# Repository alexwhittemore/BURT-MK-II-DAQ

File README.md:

BURT Mk-II DAQ
==============

Boston University Rocket Team's Mk-II Data Acquisition and Control System.

Background
----------
The Boston University Rocket Team is currently focused on advancing hybrid rocket motor design and research. The Mk-II is a static (never leaves the ground) test bed for experimentation with various design parameters like chamber and oxidizer injector geometries.

### Sensors
The DAQ side consists of multiple sensors: pressure transducers, load cells, and thermocouples.

There are two pressure transducers, each rated at 500PSI full scale. The Oxidizer Line Transducer measures the pressure on the nitrous oxide feed line right before the injector. This should match the vapor pressure of N2O, roughly 750PSI dependent on temperature. The Combustion Chamber Transducer measures the pressure INSIDE the combustion chamber, directly after the injector. For Mk-II, the design chamber pressure is 500PSI

There are also two load cells. The Thrust Load Cell is an S-Beam, 500lbs full scale load cell. Design thrust is 75lbs. The Oxidizer Tank Cell is a canteliver 50lbs cell. This measures the weight of the Nitrous Oxide tank used to feed the motor, where change in mass of the tank can be used to calculate mass flow rate of oxidizer.

There are three thermocouples. All are K-type. One NPT-threaded, sealed TC measures oxidizer temperature before the injector. One of two silicone surface adhesive TCs measures the oxidizer tank temperature. The other of these measures the combustion chamber casing temperature. A spike in this temperature indicates a fault with the fuel grain casting and a potentially unsafe conditon that could result in a burn-through of the schedule-80 steel casing.

### Boards
All of these are read by four wheatstone bridge digitizer boards (Bridge Digitizer.sch) and three K-type thermocouple digitizer boards (Thermocouple Digitizer.sch). The outputs of these boards are read via SPI by an mbed microcontroller residing on a main board. This main board also holds a zigbee radio which forwards a UART connection to a host computer for off-site (safe distance) live monitoring of the system, as well as a USB plug for a thumb drive to log the live, real-time acquired data. Additionally, a UART is broken out on a set of .1" spaced headers to connect to a sparkfun graphical LCD for on-site monitoring. Finally, two pins are broken out on a DB-9 connector to serve as software serial to a safe distance physical control interface. This could just as easily be run exclusively via zigbee radio.

### Control
The final job of the system is to control the burn itself. This is handled by two pneumatic valves, switched by 24-volt electric solenoids in turn controlled by the mbed via a quad-half H-bridge chip on the main board. These solenoids are either open or spring-shut, and thus only require two outputs of the quad half Bridge. A third output is used to control a nichrome wire-based pyrotechnic ignitor. The fourth half bridge is implemented but unused.

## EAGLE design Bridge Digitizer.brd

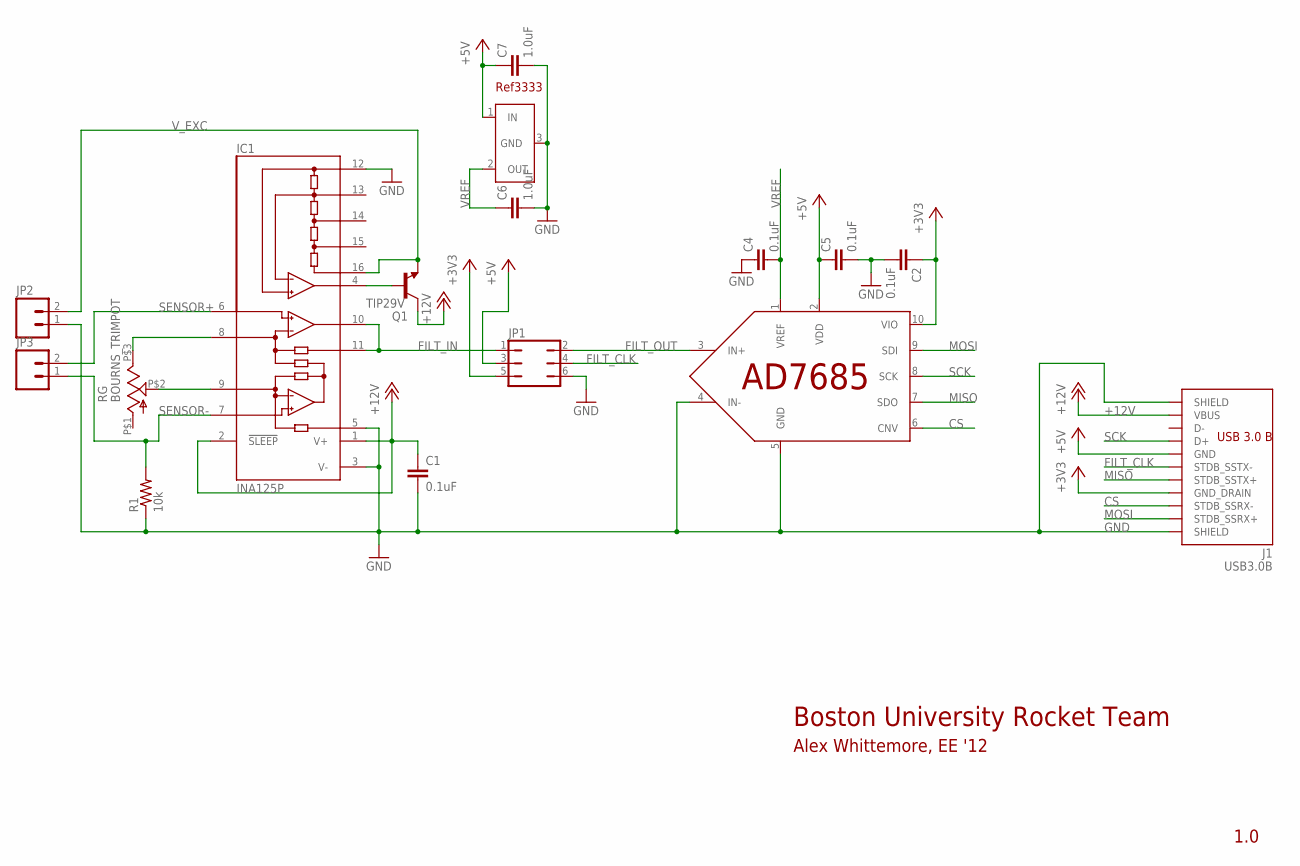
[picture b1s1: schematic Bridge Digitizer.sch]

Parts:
C1, C2, C4, C5: 0.1uF; 0402-CAP
C6, C7: 1.0uF; 0402-CAP
IC1: INA125P; DIL16
IC3: AD7685; MSOP10
IC4: REF3333; SOT23
J1: USB3.0B; AMPHENOLUSB3.0B
JP1: JP3Q
JP2, JP3: M025MM; SCREWTERMINAL-5MM-2
Q1: TIP29V; TO220V
R1: 10k; 0207/7
RG: BOURNS_TRIMPOT; 3296W

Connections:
+3V3: C2.1, IC3.10 (VIO), J1.7 (GND_DRAIN), JP1.5
+5V: C5.1, C7.1, IC3.2 (VDD), IC4.1 (IN), J1.4 (GND), JP1.3
+12V: C1.1, IC1.1 (V+), IC1.2 (!SLEEP), J1.1 (VBUS), Q1.2 (C)
CS: IC3.6 (CNV), J1.8 (STDB_SSRX-)
FILT_CLK: J1.5 (STDB_SSTX-), JP1.4
FILT_IN: IC1.10 (OUT), IC1.11 (SENSE), JP1.1
FILT_OUT: IC3.3 (IN+), JP1.2
GND: C1.2, C2.2, C4.1, C5.2, C6.2, C7.2, IC1.3 (V-), IC1.5 (REF), IC1.12 (REFCOM), IC3.4 (IN-), IC3.5 (GND), IC4.3 (GND), J1.10@1 (SHIELD), J1.10@2 (SHIELD), JP1.6, JP2.1, R1.1
MISO: IC3.7 (SDO), J1.6 (STDB_SSTX+)
MOSI: IC3.9 (SDI), J1.9 (STDB_SSRX+)
unnamed: IC1.4 (REFOUT), Q1.1 (B)
unnamed: IC1.9 (RG), RG.P$2 (2)
unnamed: IC1.8 (RG), RG.P$3 (3)
SCK: IC3.8 (SCK), J1.3 (D+)
SENSOR+: IC1.6 (+IN), JP3.2
SENSOR-: IC1.7 (-IN), JP3.1, R1.2
VREF: C4.2, C6.1, IC3.1 (VREF), IC4.2 (OUT)
V_EXC: IC1.16 (REF10), JP2.2, Q1.3 (E)

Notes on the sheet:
Boston University Rocket Team
1.0
Alex Whittemore, EE '12

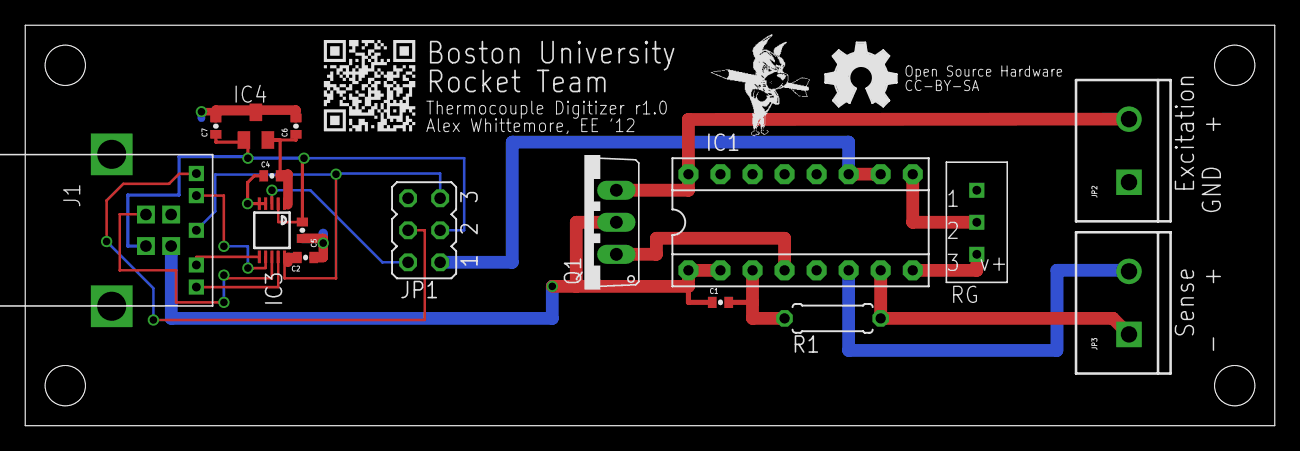
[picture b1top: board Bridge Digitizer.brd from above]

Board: 2 copper layers, 99.1 x 31.8 mm, 17 parts (0 on the bottom side), 18 nets.

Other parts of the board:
U$1: OSHW_FILLX200_NOTEXT

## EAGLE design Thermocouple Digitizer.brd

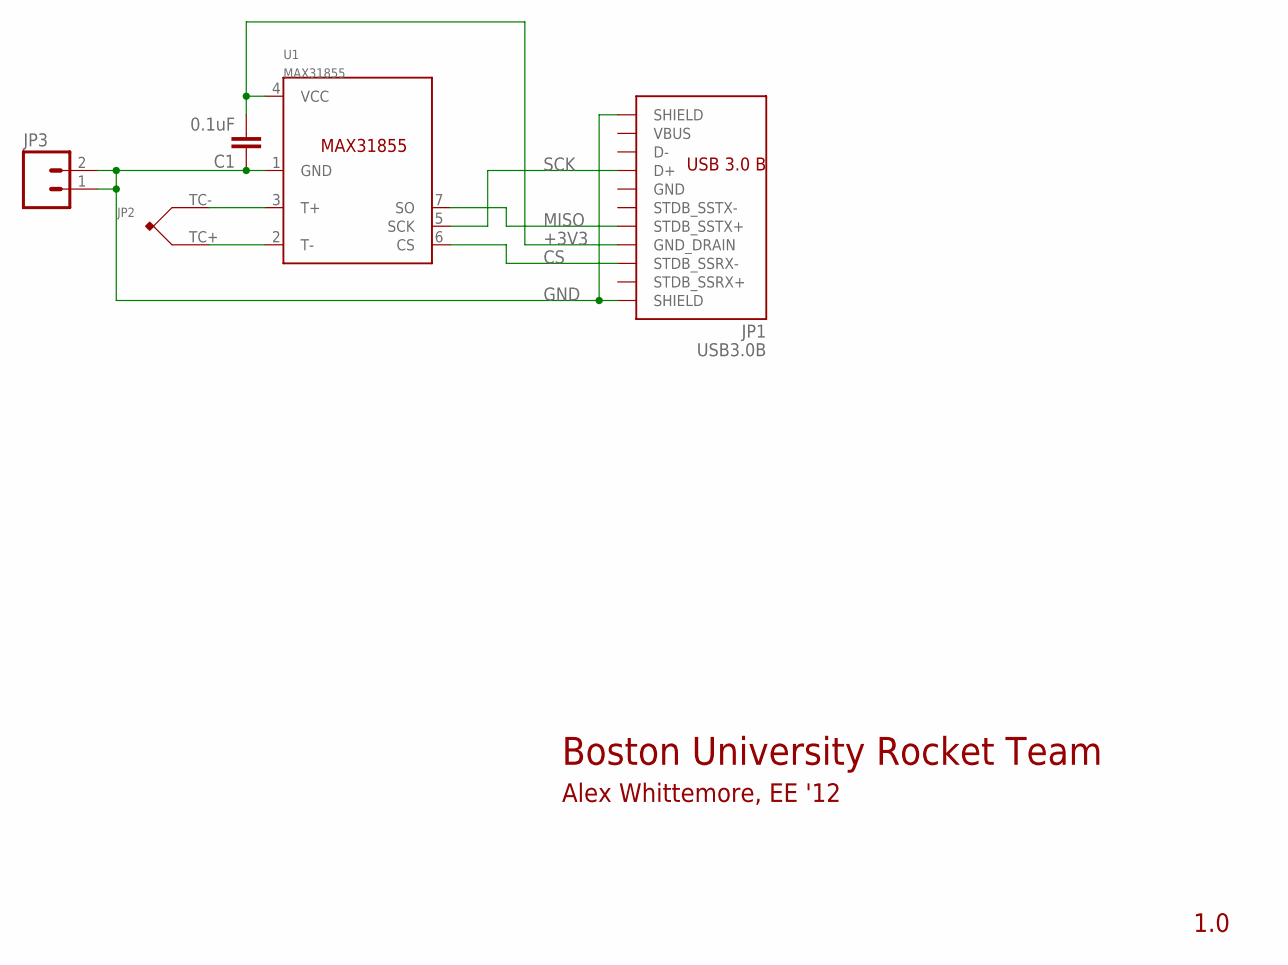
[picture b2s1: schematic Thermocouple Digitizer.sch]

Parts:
C1: 0.1uF; 0402-CAP
JP1: USB3.0B; AMPHENOLUSB3.0B
JP2: OMEGA_PCC-SMP
JP3: M025MM; SCREWTERMINAL-5MM-2
U1: MAX31855; SOIC8

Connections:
+3V3: C1.2, JP1.7 (GND_DRAIN), U1.4 (VCC)
CS: JP1.8 (STDB_SSRX-), U1.6 (CS)
GND: C1.1, JP1.10@1 (SHIELD), JP1.10@2 (SHIELD), JP3.1, JP3.2, U1.1 (GND)
MISO: JP1.6 (STDB_SSTX+), U1.7 (SO)
unnamed: JP2.TC-, U1.3 (T+)
unnamed: JP2.TC+, U1.2 (T-)
SCK: JP1.3 (D+), U1.5 (SCK)

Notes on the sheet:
Boston University Rocket Team
Alex Whittemore, EE '12
1.0

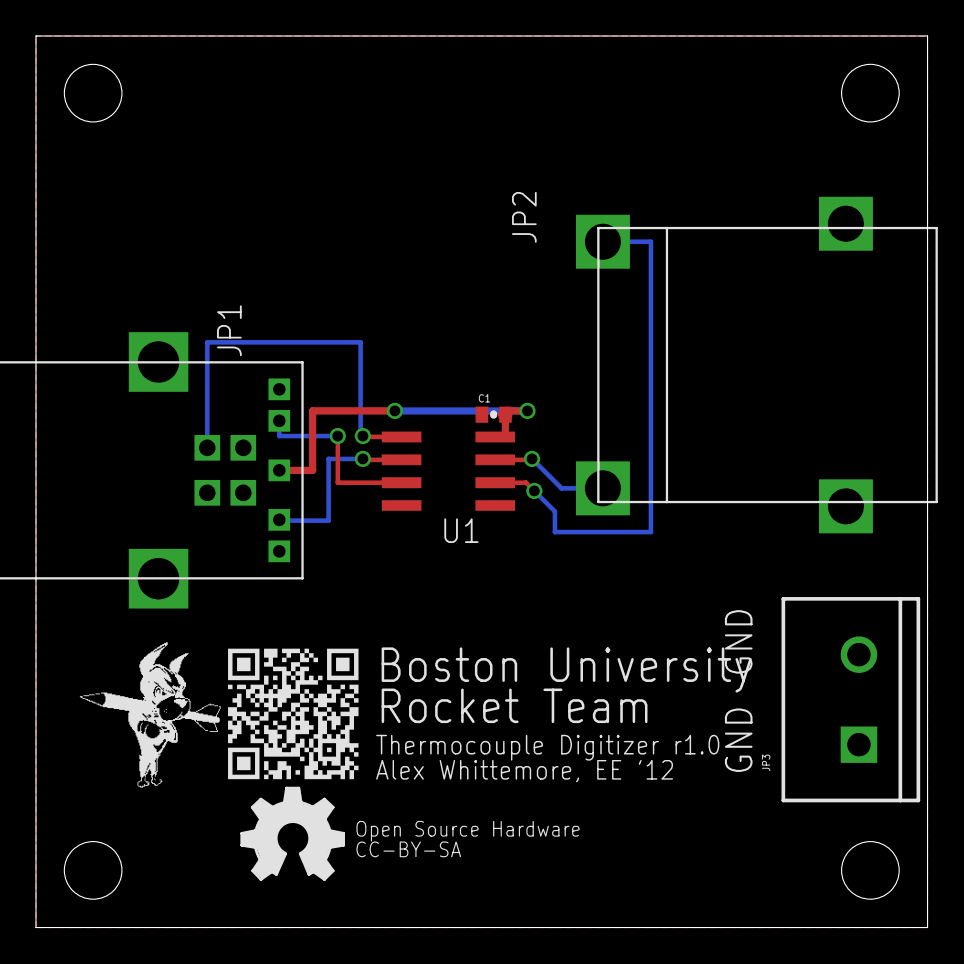
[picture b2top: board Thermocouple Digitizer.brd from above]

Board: 2 copper layers, 49.5 x 49.5 mm, 6 parts (0 on the bottom side), 7 nets.

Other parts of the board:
U$1: OSHW_FILLX200_NOTEXT

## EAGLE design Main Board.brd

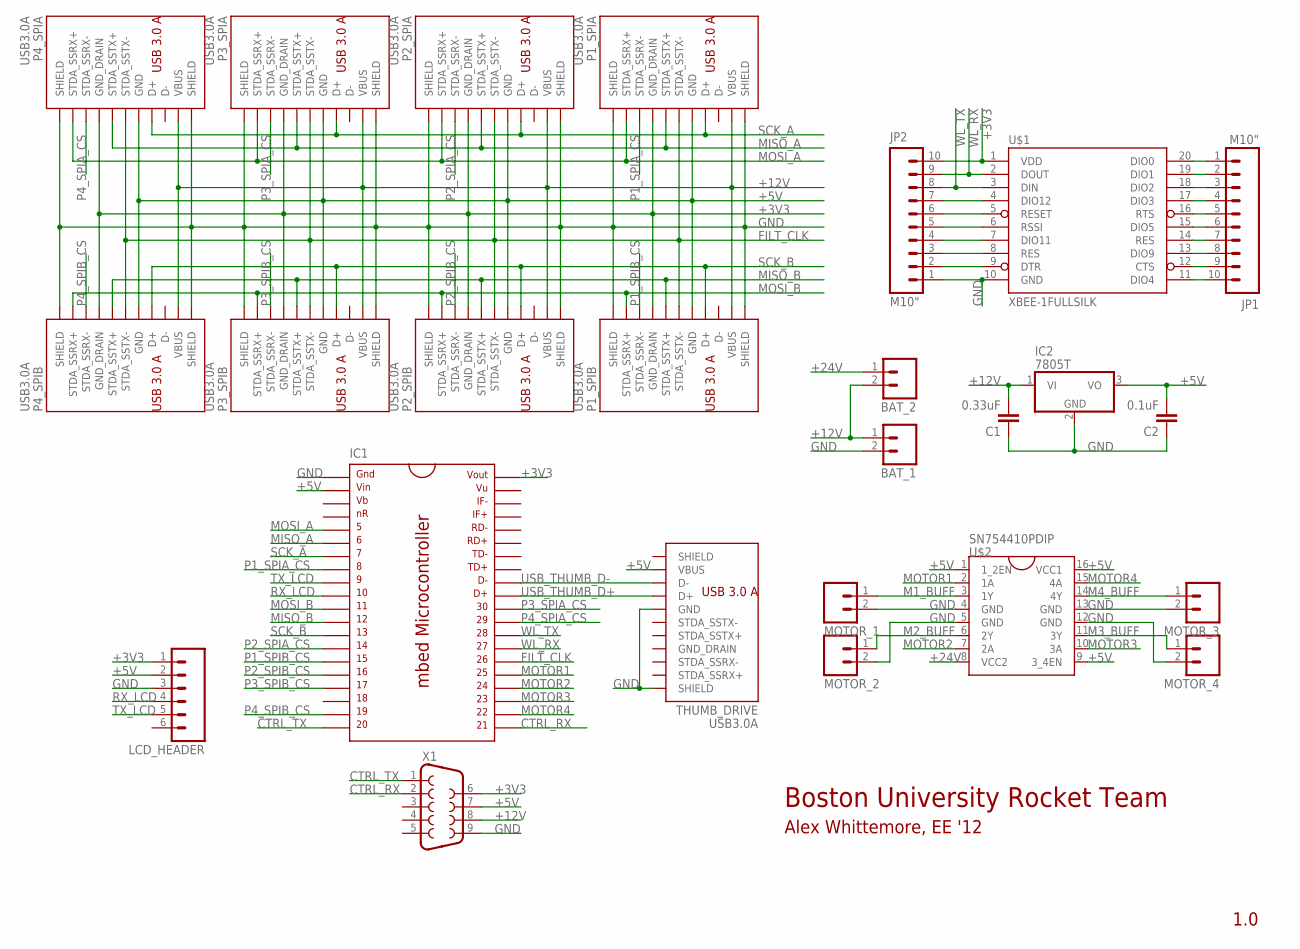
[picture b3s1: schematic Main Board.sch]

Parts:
BAT_1, BAT_2: M025MM; SCREWTERMINAL-5MM-2
C1: 0.33uF; 0402-CAP
C2: 0.1uF; 0402-CAP
IC1: MBED_MICROCONTROLLER; DIL40_0.9
IC2: 7805T; TO220H
JP1, JP2: M10"; 1X10
LCD_HEADER: M06LOCK; 1X06_LOCK
MOTOR_1, MOTOR_2, MOTOR_3, MOTOR_4: M025MM; SCREWTERMINAL-5MM-2
P1_SPIA, P1_SPIB, P2_SPIA, P2_SPIB, P3_SPIA, P3_SPIB, P4_SPIA, P4_SPIB: USB3.0A; AMPHENOLUSB3.0A
THUMB_DRIVE: USB3.0A; AMPHENOLUSB3.0A
U$1: XBEE-1FULLSILK; XBEE
U$2: SN754410PDIP; DIL16
X1: DB9MALE; DB9_MALE

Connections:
+3V3: IC1.40, JP2.10, LCD_HEADER.1, P1_SPIA.7 (GND_DRAIN), P1_SPIB.7 (GND_DRAIN), P2_SPIA.7 (GND_DRAIN), P2_SPIB.7 (GND_DRAIN), P3_SPIA.7 (GND_DRAIN), P3_SPIB.7 (GND_DRAIN), P4_SPIA.7 (GND_DRAIN), P4_SPIB.7 (GND_DRAIN), U$1.1 (VDD), X1.6
+5V: C2.2, IC1.2, IC2.3 (VO), LCD_HEADER.2, P1_SPIA.4 (GND), P1_SPIB.4 (GND), P2_SPIA.4 (GND), P2_SPIB.4 (GND), P3_SPIA.4 (GND), P3_SPIB.4 (GND), P4_SPIA.4 (GND), P4_SPIB.4 (GND), THUMB_DRIVE.1 (VBUS), U$2.1 (1_2EN), U$2.9 (3_4EN), U$2.16 (VCC1), X1.7
+12V: BAT_1.1, BAT_2.2, C1.2, IC2.1 (VI), P1_SPIA.1 (VBUS), P1_SPIB.1 (VBUS), P2_SPIA.1 (VBUS), P2_SPIB.1 (VBUS), P3_SPIA.1 (VBUS), P3_SPIB.1 (VBUS), P4_SPIA.1 (VBUS), P4_SPIB.1 (VBUS), X1.8
+24V: BAT_2.1, U$2.8 (VCC2)
CTRL_RX: IC1.21, X1.2
CTRL_TX: IC1.20, X1.1
FILT_CLK: IC1.26, P1_SPIA.8 (STDA_SSTX-), P1_SPIB.8 (STDA_SSTX-), P2_SPIA.8 (STDA_SSTX-), P2_SPIB.8 (STDA_SSTX-), P3_SPIA.8 (STDA_SSTX-), P3_SPIB.8 (STDA_SSTX-), P4_SPIA.8 (STDA_SSTX-), P4_SPIB.8 (STDA_SSTX-)
GND: BAT_1.2, C1.1, C2.1, IC1.1, IC2.2 (GND), JP2.1, LCD_HEADER.3, MOTOR_1.2, MOTOR_2.2, MOTOR_3.2, MOTOR_4.2, P1_SPIA.10@1 (SHIELD), P1_SPIA.10@2 (SHIELD), P1_SPIB.10@1 (SHIELD), P1_SPIB.10@2 (SHIELD), P2_SPIA.10@1 (SHIELD), P2_SPIA.10@2 (SHIELD), P2_SPIB.10@1 (SHIELD), P2_SPIB.10@2 (SHIELD), P3_SPIA.10@1 (SHIELD), P3_SPIA.10@2 (SHIELD), P3_SPIB.10@1 (SHIELD), P3_SPIB.10@2 (SHIELD), P4_SPIA.10@1 (SHIELD), P4_SPIA.10@2 (SHIELD), P4_SPIB.10@1 (SHIELD), P4_SPIB.10@2 (SHIELD), THUMB_DRIVE.4 (GND), THUMB_DRIVE.10@2 (SHIELD), U$1.10 (GND), U$2.4 (GND), U$2.5 (GND), U$2.12 (GND), U$2.13 (GND), X1.9
M1_BUFF: MOTOR_1.1, U$2.3 (1Y)
M2_BUFF: MOTOR_2.1, U$2.6 (2Y)
M3_BUFF: MOTOR_4.1, U$2.11 (3Y)
M4_BUFF: MOTOR_3.1, U$2.14 (4Y)
MISO_A: IC1.6, P1_SPIA.9 (STDA_SSTX+), P2_SPIA.9 (STDA_SSTX+), P3_SPIA.9 (STDA_SSTX+), P4_SPIA.9 (STDA_SSTX+)
MISO_B: IC1.12, P1_SPIB.9 (STDA_SSTX+), P2_SPIB.9 (STDA_SSTX+), P3_SPIB.9 (STDA_SSTX+), P4_SPIB.9 (STDA_SSTX+)
MOSI_A: IC1.5, P1_SPIA.6 (STDA_SSRX+), P2_SPIA.6 (STDA_SSRX+), P3_SPIA.6 (STDA_SSRX+), P4_SPIA.6 (STDA_SSRX+)
MOSI_B: IC1.11, P1_SPIB.6 (STDA_SSRX+), P2_SPIB.6 (STDA_SSRX+), P3_SPIB.6 (STDA_SSRX+), P4_SPIB.6 (STDA_SSRX+)
MOTOR1: IC1.25, U$2.2 (1A)
MOTOR2: IC1.24, U$2.7 (2A)
MOTOR3: IC1.23, U$2.10 (3A)
MOTOR4: IC1.22, U$2.15 (4A)
unnamed: JP2.7, U$1.4 (DIO12)
unnamed: JP2.6, U$1.5 (RESET)
unnamed: JP2.5, U$1.6 (RSSI)
unnamed: JP2.4, U$1.7 (DIO11)
unnamed: JP2.3, U$1.8 (RES)
unnamed: JP2.2, U$1.9 (DTR)
unnamed: JP1.1, U$1.20 (DIO0)
unnamed: JP1.2, U$1.19 (DIO1)
unnamed: JP1.3, U$1.18 (DIO2)
unnamed: JP1.4, U$1.17 (DIO3)
unnamed: JP1.5, U$1.16 (RTS)
unnamed: JP1.6, U$1.15 (DIO5)
unnamed: JP1.7, U$1.14 (RES)
unnamed: JP1.8, U$1.13 (DIO9)
unnamed: JP1.9, U$1.12 (CTS)
unnamed: JP1.10, U$1.11 (DIO4)
P1_SPIA_CS: IC1.8, P1_SPIA.5 (STDA_SSRX-)
P1_SPIB_CS: IC1.15, P1_SPIB.5 (STDA_SSRX-)
P2_SPIA_CS: IC1.14, P2_SPIA.5 (STDA_SSRX-)
P2_SPIB_CS: IC1.16, P2_SPIB.5 (STDA_SSRX-)
P3_SPIA_CS: IC1.30, P3_SPIA.5 (STDA_SSRX-)
P3_SPIB_CS: IC1.17, P3_SPIB.5 (STDA_SSRX-)
P4_SPIA_CS: IC1.29, P4_SPIA.5 (STDA_SSRX-)
P4_SPIB_CS: IC1.19, P4_SPIB.5 (STDA_SSRX-)
RX_LCD: IC1.10, LCD_HEADER.4
SCK_A: IC1.7, P1_SPIA.3 (D+), P2_SPIA.3 (D+), P3_SPIA.3 (D+), P4_SPIA.3 (D+)
SCK_B: IC1.13, P1_SPIB.3 (D+), P2_SPIB.3 (D+), P3_SPIB.3 (D+), P4_SPIB.3 (D+)
TX_LCD: IC1.9, LCD_HEADER.5
USB_THUMB_D+: IC1.31, THUMB_DRIVE.3 (D+)
USB_THUMB_D-: IC1.32, THUMB_DRIVE.2 (D-)
WL_RX: IC1.27, JP2.9, U$1.2 (DOUT)
WL_TX: IC1.28, JP2.8, U$1.3 (DIN)

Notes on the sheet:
Boston University Rocket Team
Alex Whittemore, EE '12
1.0

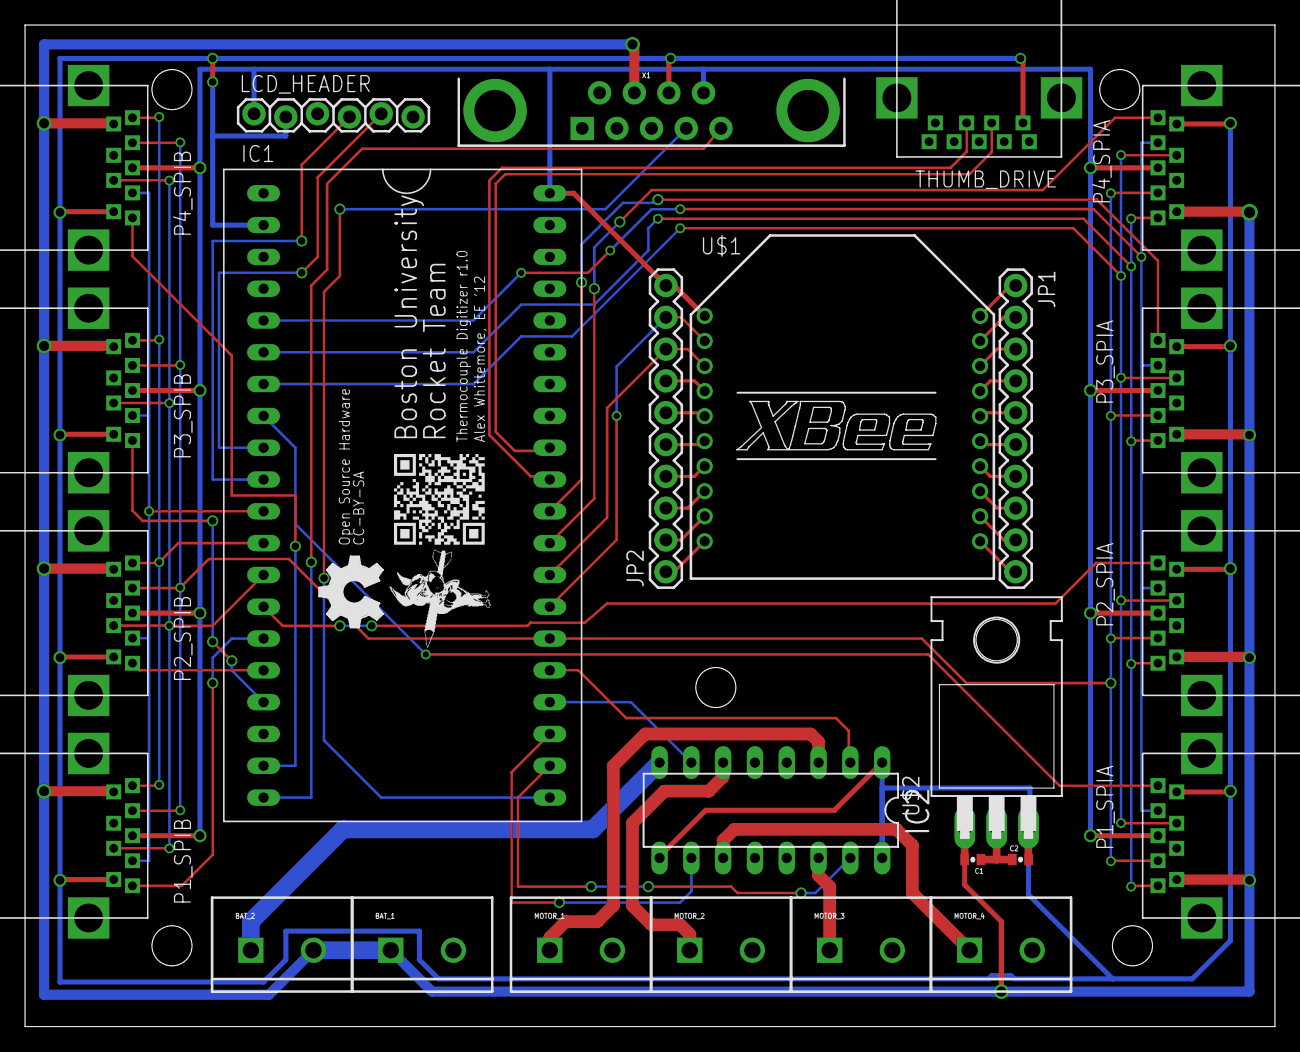
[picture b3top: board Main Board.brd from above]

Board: 2 copper layers, 99.8 x 80.0 mm, 27 parts (1 on the bottom side), 52 nets.

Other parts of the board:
U$3, U$4: OSHW_FILLX200_NOTEXT

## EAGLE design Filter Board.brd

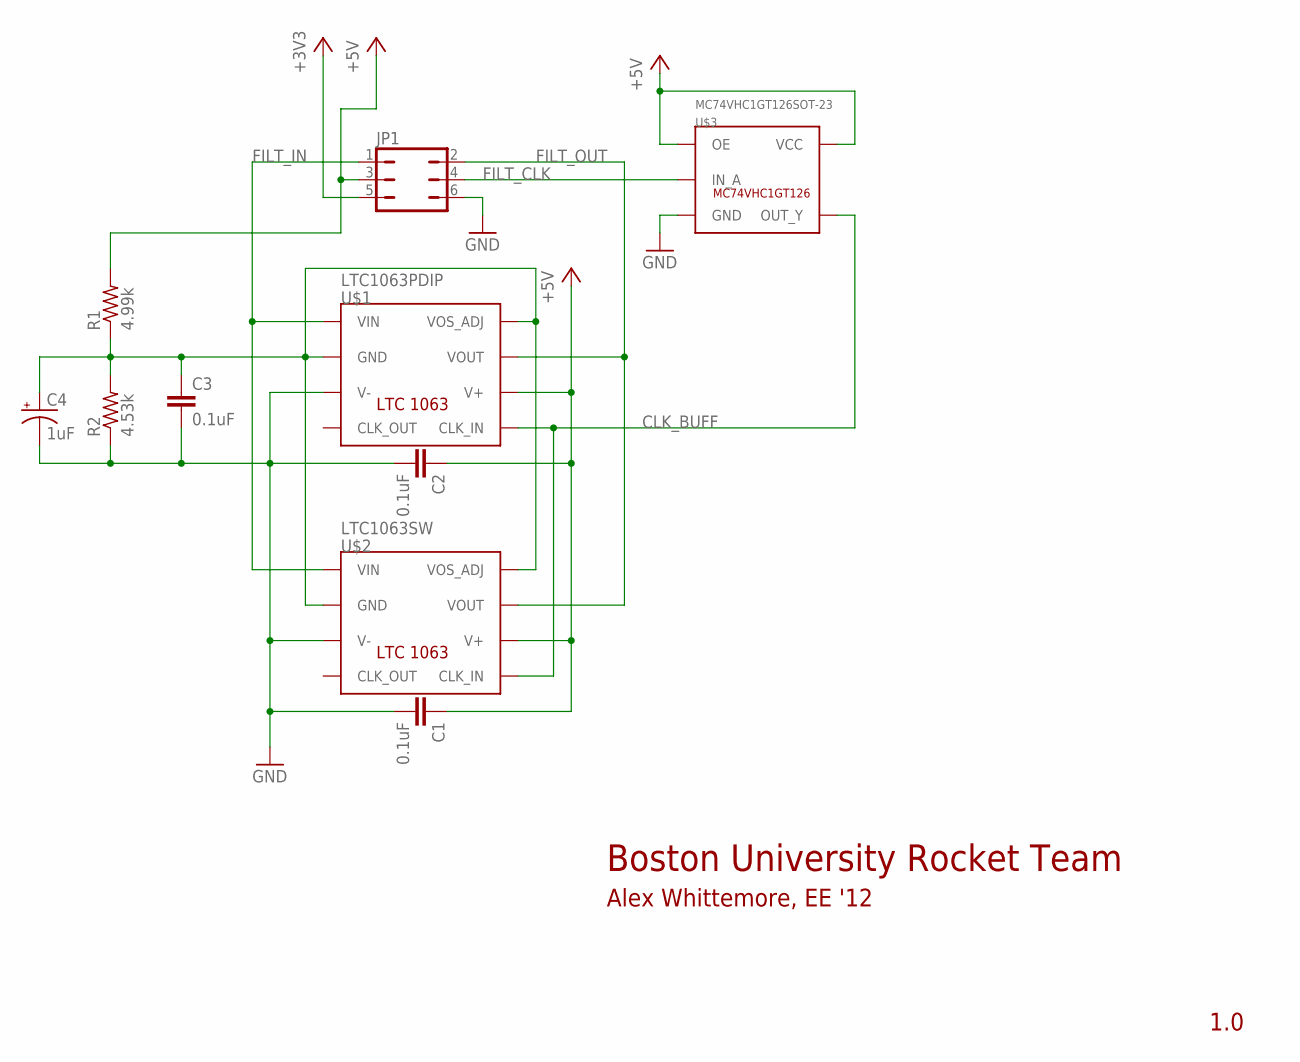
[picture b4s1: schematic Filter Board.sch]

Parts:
C1, C2, C3: 0.1uF; 0402-CAP
C4: 1uF; EIA3216
JP1: JP3Q
R1: 4.99k; 0207/7
R2: 4.53k; 0207/7
U$1: LTC1063PDIP; SOCKED-08
U$2: LTC1063SW; SOP16
U$3: MC74VHC1GT126SOT-23; SOT23-5L

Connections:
+3V3: JP1.5
+5V: C1.1, C2.1, JP1.3, R1.2, U$1.6 (V+), U$2.12 (V+), U$3.1 (OE), U$3.5 (VCC)
CLK_BUFF: U$1.5 (CLK_IN), U$2.9 (CLK_IN), U$3.4 (OUT_Y)
FILT_CLK: JP1.4, U$3.2 (IN_A)
FILT_IN: JP1.1, U$1.1 (VIN), U$2.2 (VIN)
FILT_OUT: JP1.2, U$1.7 (VOUT), U$2.14 (VOUT)
GND: C1.2, C2.2, C3.2, C4.C (-), JP1.6, R2.1, U$1.3 (V-), U$2.5 (V-), U$3.3 (GND)
unnamed: C3.1, C4.A (+), R1.1, R2.2, U$1.2 (GND), U$1.8 (VOS_ADJ), U$2.3 (GND), U$2.16 (VOS_ADJ)

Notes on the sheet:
Boston University Rocket Team
1.0
Alex Whittemore, EE '12

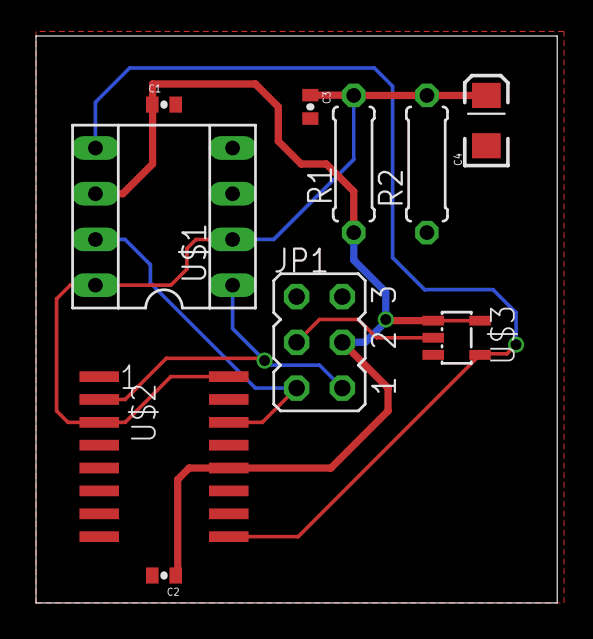
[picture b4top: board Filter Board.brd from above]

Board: 2 copper layers, 29.0 x 31.5 mm, 10 parts (0 on the bottom side), 7 nets.

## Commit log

2011-10-25 Initial commit of four boards, all rev1.0.
2011-10-25 Added a README
2011-10-25 Added final taped-out rev1.0 gerber files for all boards.
2011-11-12 Added r1.0 main board PDFs for reference.
2011-11-30 Added a list of some parts and numbers used.
2011-12-19 Converted to new Eagle V6 XML format
2013-06-20 ignore eagle.epf

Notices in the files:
Bridge Digitizer.brd:
CC-BY-SA
